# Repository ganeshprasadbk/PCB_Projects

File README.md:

# PCB_Projects
This repository hosts a series of PCB designing projects that I tried while learning or as hobby projects

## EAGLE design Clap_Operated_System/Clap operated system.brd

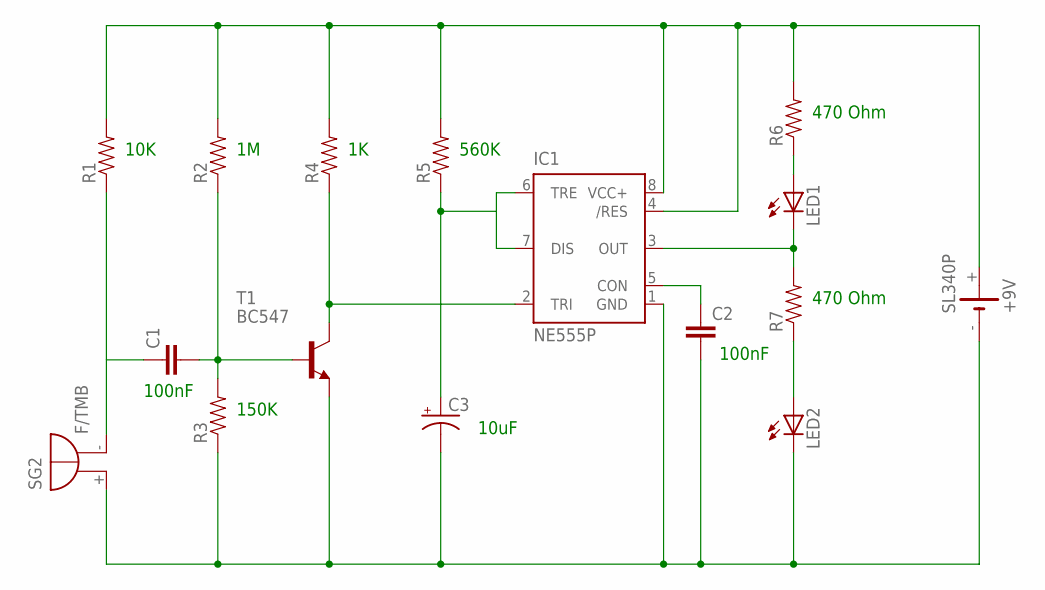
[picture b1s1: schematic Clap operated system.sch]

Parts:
+9V: SL340P; SL-340/P3.6V
C1, C2: 0.1UF-50V-20%(PTH)KIT-EZ; CAP-PTH-SMALL-KIT
C3: CAP_POLPTH1; CPOL-RADIAL-100UF-25V
IC1: NE555P; DIL-08
LED1, LED2: LED5MM
R1, R2, R3, R4, R5, R6, R7: 10KOHM1/6W5%(PTH)KIT; AXIAL-0.3-KIT
SG2: F/TMB
T1: BC547; TO92

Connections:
unnamed: C1.1, R1.P$1 (1), SG2.-
unnamed: C1.2, R2.P$1 (1), R3.P$2 (2), T1.2 (B)
unnamed: IC1.2 (TRI), R4.P$1 (1), T1.3 (C)
unnamed: C3.1 (+), IC1.6 (TRE), IC1.7 (DIS), R5.P$1 (1)
unnamed: C2.1, IC1.5 (CON)
unnamed: IC1.3 (OUT), LED1.K (C), R7.P$2 (2)
unnamed: LED2.A, R7.P$1 (1)
unnamed: +9V.+, IC1.4 (/RES), IC1.8 (VCC+), R1.P$2 (2), R2.P$2 (2), R4.P$2 (2), R5.P$2 (2), R6.P$2 (2)
unnamed: LED1.A, R6.P$1 (1)
unnamed: +9V.-, C2.2, C3.2 (-), IC1.1 (GND), LED2.K (C), R3.P$1 (1), SG2.+, T1.1 (E)

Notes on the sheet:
10K
150K
560K
470 Ohm
10uF
100nF

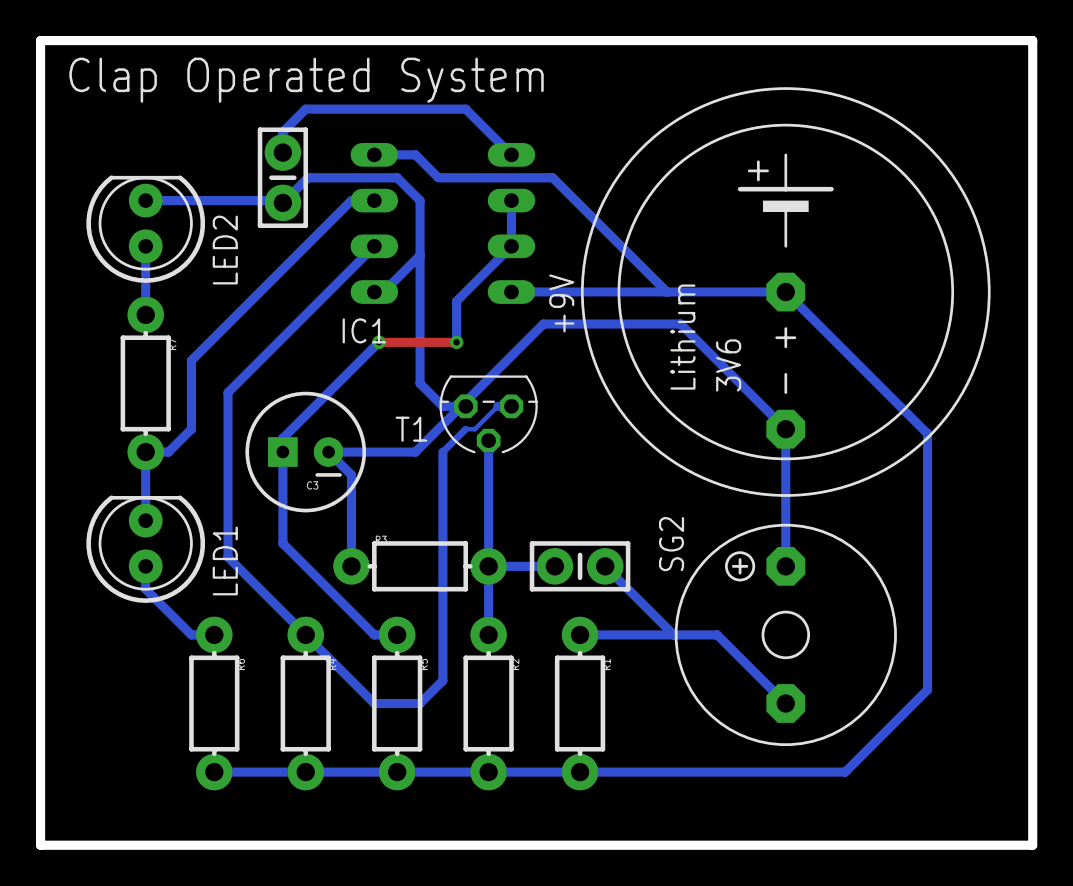
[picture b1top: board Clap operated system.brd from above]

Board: 2 copper layers, 55.1 x 44.7 mm, 16 parts (1 on the bottom side), 10 nets.

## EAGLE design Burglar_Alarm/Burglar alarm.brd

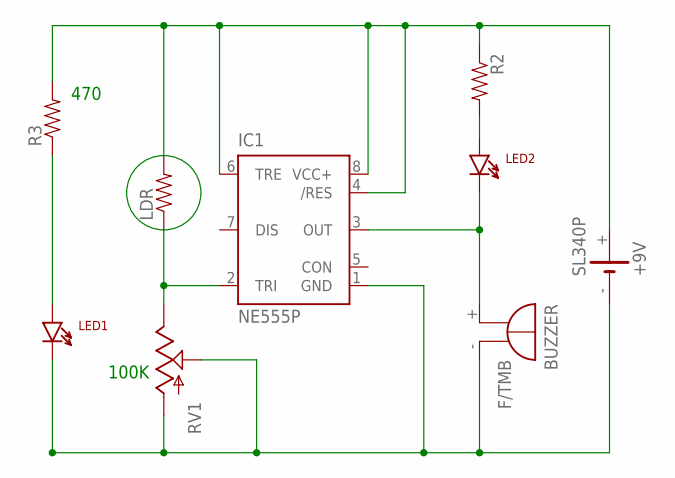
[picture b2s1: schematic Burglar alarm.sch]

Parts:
+9V: SL340P; SL-340/P3.6V
BUZZER: F/TMB
IC1: NE555P; DIL-08
LDR: RESISTORAXIAL-0.3; AXIAL-0.3
LED1, LED2: LTE-302
R2, R3: RESISTORAXIAL-0.3; AXIAL-0.3
RV1: POTTRIM; TRIM_POT

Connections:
unnamed: IC1.2 (TRI), LDR.P$1 (1), RV1.2 (E)
unnamed: BUZZER.+, IC1.3 (OUT), LED2.C
unnamed: LED2.A, R2.P$2 (2)
unnamed: LED1.A, R3.P$1 (1)
unnamed: +9V.+, IC1.4 (/RES), IC1.6 (TRE), IC1.8 (VCC+), LDR.P$2 (2), R2.P$1 (1), R3.P$2 (2)
unnamed: +9V.-, BUZZER.-, IC1.1 (GND), LED1.C, RV1.1 (S), RV1.3 (A)

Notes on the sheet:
100K
470

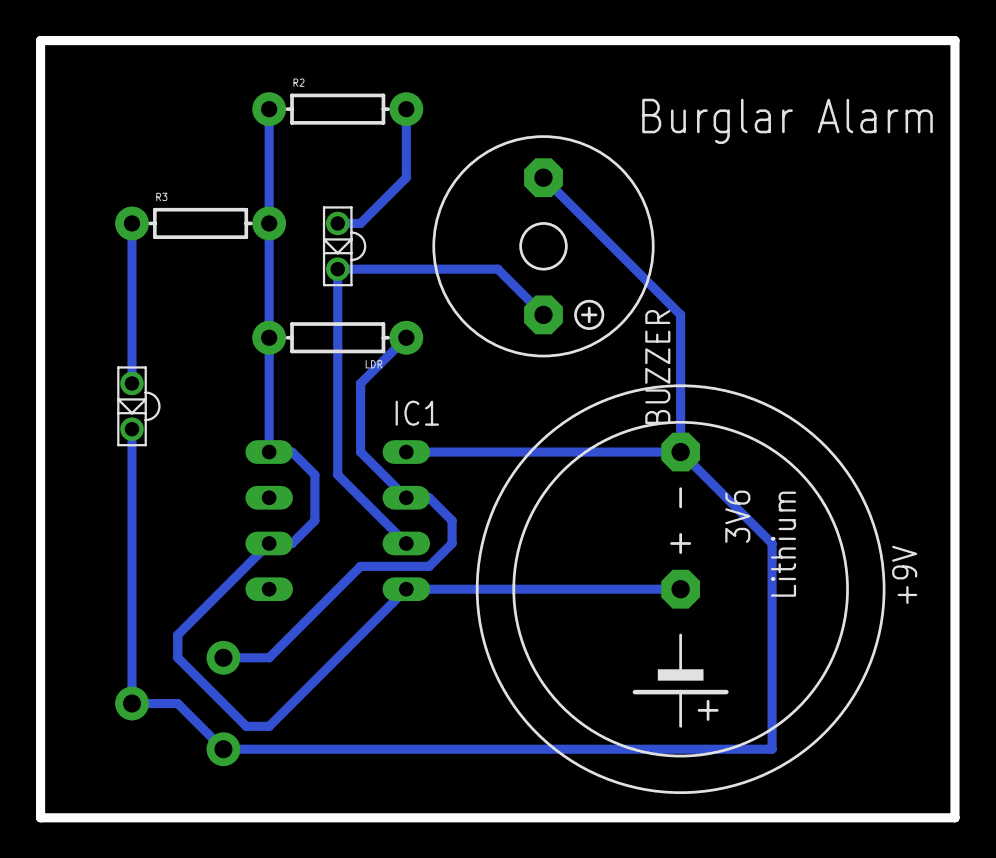
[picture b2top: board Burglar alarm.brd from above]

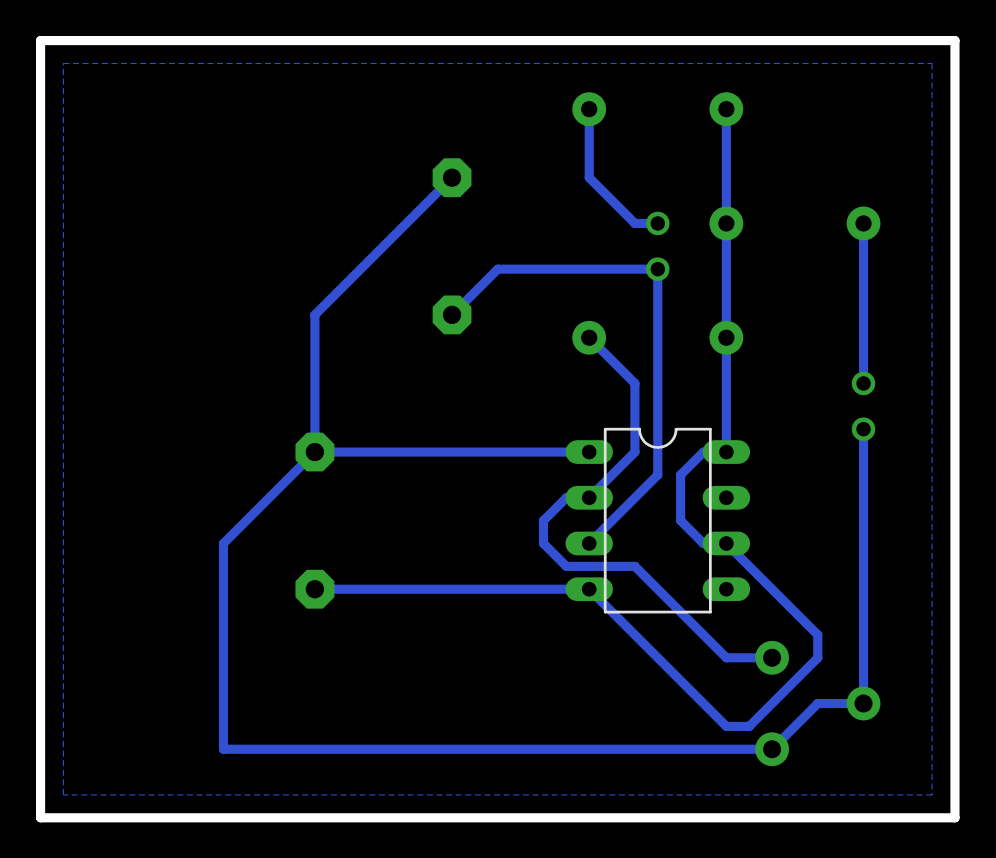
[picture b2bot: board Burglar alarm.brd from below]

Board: 2 copper layers, 50.8 x 43.2 mm, 9 parts (2 on the bottom side), 6 nets.

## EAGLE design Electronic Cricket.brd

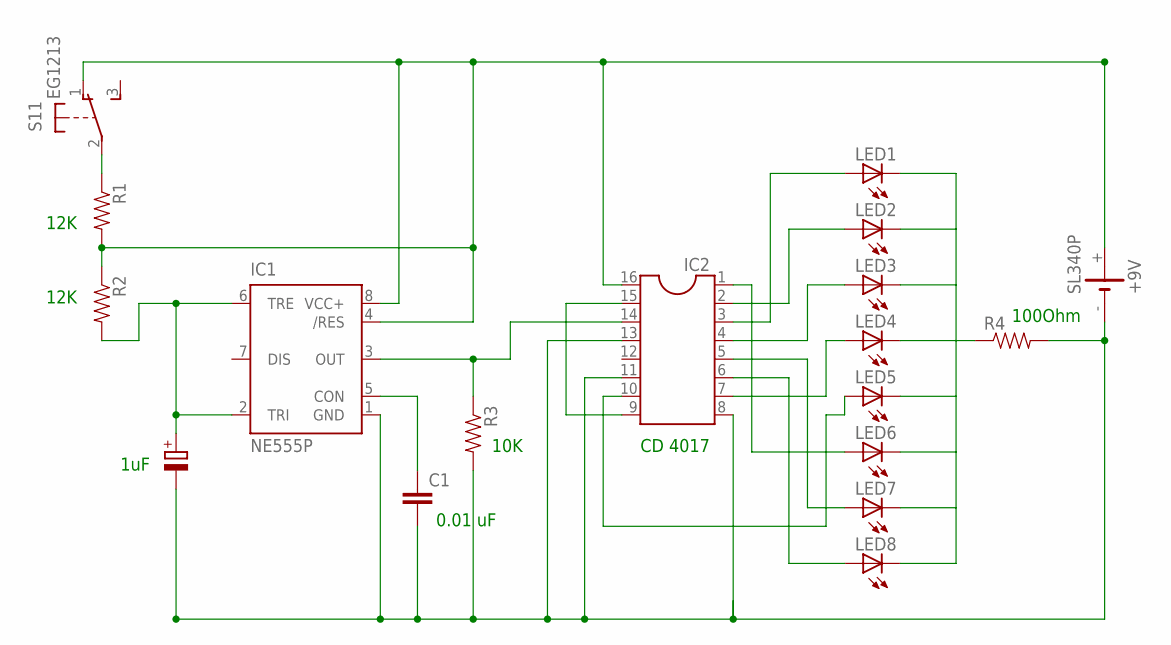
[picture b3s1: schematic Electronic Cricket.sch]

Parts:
+9V: SL340P; SL-340/P3.6V
C1: C2.5/6; C2.5-6
IC1: NE555P; DIL-08
IC2: DIL16
LED1, LED2, LED3, LED4, LED5, LED6, LED7, LED8: LEDB156; Q62902-B156
R1, R2, R3, R4: RESISTORAXIAL-0.3; AXIAL-0.3
S1: EG1213

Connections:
unnamed: IC2.3, LED1.A
unnamed: IC2.2, LED2.A
unnamed: IC2.4, LED3.A
unnamed: IC2.7, LED4.A
unnamed: IC2.10, LED5.A
unnamed: IC2.1, LED6.A
unnamed: IC2.5, LED7.A
unnamed: IC2.9, IC2.15
unnamed: +9V.-, C1.2, IC1.1 (GND), IC2.8, IC2.11, IC2.13, R3.P$2 (2), R4.P$2 (2)
unnamed: IC2.6, LED8.A
unnamed: R1.P$1 (1), S1.2
unnamed: LED1.K (C), LED2.K (C), LED3.K (C), LED4.K (C), LED5.K (C), LED6.K (C), LED7.K (C), LED8.K (C), R4.P$1 (1)
unnamed: IC1.3 (OUT), IC2.14, R3.P$1 (1)
unnamed: +9V.+, IC1.4 (/RES), IC1.8 (VCC+), IC2.16, R1.P$2 (2), R2.P$1 (1), S1.1 (O)
unnamed: IC1.2 (TRI), IC1.6 (TRE), R2.P$2 (2)
unnamed: C1.1, IC1.5 (CON)

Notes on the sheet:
12K
10K
100Ohm
1uF
0.01 uF
CD 4017

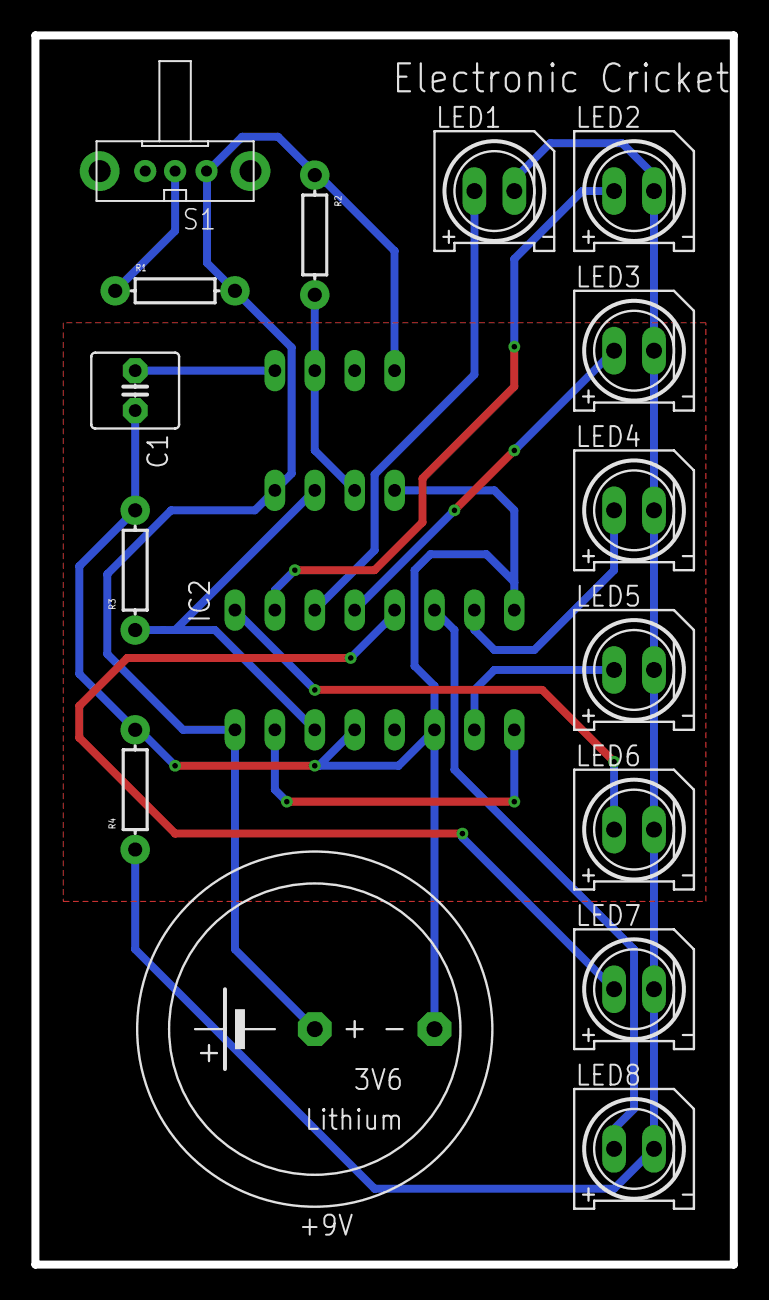
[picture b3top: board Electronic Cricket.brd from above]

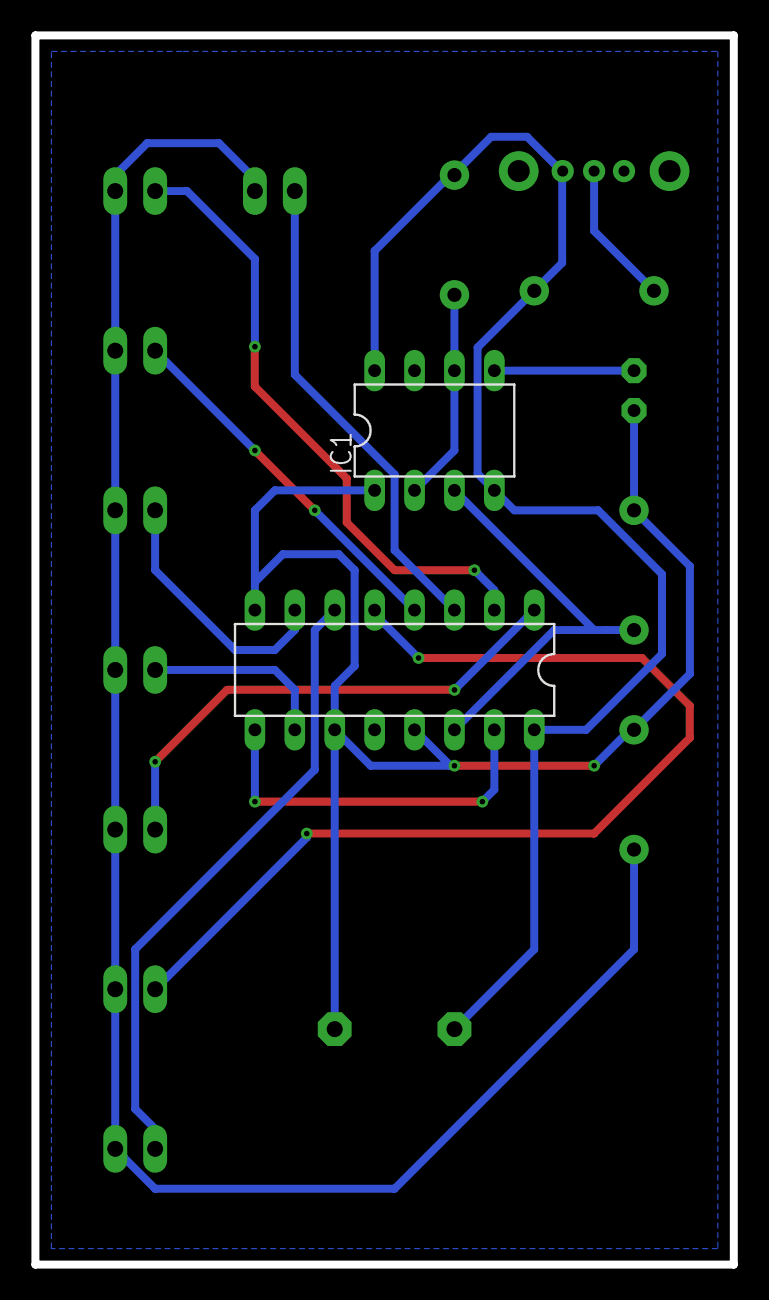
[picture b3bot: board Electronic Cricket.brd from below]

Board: 2 copper layers, 44.4 x 78.2 mm, 17 parts (2 on the bottom side), 16 nets.

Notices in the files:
parts and their libraries:
SparkFun-AnalogIC: Licensing: CC v3.0 Share-Alike You are welcome to use this library for commercial purposes.
SparkFun-Retired: Licensing: Creative Commons ShareAlike 4.0 International - https://creativecommons.org/licenses/by-sa/4.0
